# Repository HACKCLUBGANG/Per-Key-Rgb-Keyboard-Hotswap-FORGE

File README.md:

# Per-Key-Led-Keyboard-Hotswap-FORGE

Source Link Onshape -  https://cad.onshape.com/documents/a3706bff300e93766397b60f/w/be6071b581e0c225a171638b/e/79bd546bad59e5e5cdb5a4cd?renderMode=0&uiState=6af5ff969d34894ea51fd6a4
---------------------------------------
Render

Onshape

This is the Per-Key-Led-Keyboard-Hotswap which says in its name that it has per key ice blue led
It also has kailh hotswap attachment so u can also switch keys without worrying about opening the keyboard
Each key has a south facing smd ice blue led under the switch.

Heres A Render Of The Whole Build

https://github.com/user-attachments/assets/ba00d72b-443f-43d3-ab56-3a87e9c14a67

# Features 
- Per Key Rgb Customizable
- Hotswappable
- Compact  60%  10.1cm X 29.2 cm
- Usb C Powered
- 3d Printed Case
- Rp Pi Pico Fitted Into A Compact Keyboard
- 2 Layer Pcb
- Custom Made Led Circuitry
 Cool Looking :>

# Schematics 
Files in /PcbandSchem

#  Printed Circuit Board PCB
Files in /PcbandSchem

Front  Copper 

Back Copper

Both Layers

# Cad
Files in /CAD
Bottom   Plate

Top Plate

Both

# BOM
| # | Component | Part Number / Model | Qty Needed | Qty Purchased | Price (INR) | Product Link |
|---:|---|---|---:|---:|---:|---|
| 1 | Custom PCB + Shipping | JLCPCB FR-4 | 1 | 1 | ~2665 | [JLCPCB](https://jlcpcb.com/) |
| 2 | Microcontroller | Raspberry Pi Pico (RP2040) | 1 | 1 | 422 | [Robu](https://robu.in/) |
| 3 | USB-C Female Connector | Hroparts TYPE-C-31-M-13A (R250302) | 1 | 1 | 27 | [Robu](https://robu.in/product/type-c-31-m-13a-hroparts-5a-1-recessed-mount-16p-female-30%e2%84%8380-type-c-smd-usb-connectors-rohs/) |
| 4 | USB-A to Micro-USB Cable | 80cm | 1 | 1 | 59 | [Robu](https://robu.in/) |
| 5 | Micro-USB Male Connector | YT2153Y | 1 | 1 | 79 | [Robu](https://robu.in/) |
| 6 | LED Driver IC | TLC5948APWPR | 4 | 4 | 1144 | [Robu](https://robu.in/) |
| 7 | Ice-Blue LEDs | XINGLIGHT XL-2835BGWC-05 | 61 | 85 | 102 | [Robu](https://robu.in/) |
| 8 | Switching Diodes | Slkor 1N4148W SOD-123 | 61 | 70 | 72.80 | [Robu](https://robu.in/) |
| 9 | Ceramic Capacitors | 100nF, 1206, 50V | 4 | 4 | 32 | [Robu](https://robu.in/) |
| 10 | Bulk Capacitor | Taiyo Yuden EMK325ABJ107MM-T, 100µF 16V | 1 | 1 | 292.19* | [Taiyo Yuden](https://www.yuden.co.jp/) |
| 11 | Resistors | 10kΩ, 1206 | 4 | 12 | 10.56 | [Robu](https://robu.in/) |
| 12 | Resistors | 5.1kΩ, 1206 | 2 | 48 | 10.08 | [Robu](https://robu.in/) |
| 13 | Resistors | Yageo AC1206FR-07200RL, 200Ω | 0 required for IREF | 25 | 10.25 | [Robu](https://robu.in/) |
| 14 | Mechanical Switches | Gateron G Pro 3.0 Yellow | 61 | 70 (7 packs) | 1253.70 | [Meckeys](https://meckeys.com/) |
| 15 | Hot-Swap Sockets | Kailh MX Hot-Swap Socket, White | 61 | 7 listings | 504 | [Meckeys](https://meckeys.com/) |
| 16 | Stabilizers | DesignerStudio Plate Stabilizers | 4 × 2U + 1 × 6.25U | 1 kit | 550 | [Keyora](https://keyora.store/products/designerstudio-100-plate-mount-stabilizers-adaptive-wire-pom) |
| 17 | Keycaps | Selected keycap set | 1 set | 1 set | 799 | — |

## Notes
- Robu has a minimum order value of ₹10 per item.
- PCB + shipping is approximately $29 (₹2,665).

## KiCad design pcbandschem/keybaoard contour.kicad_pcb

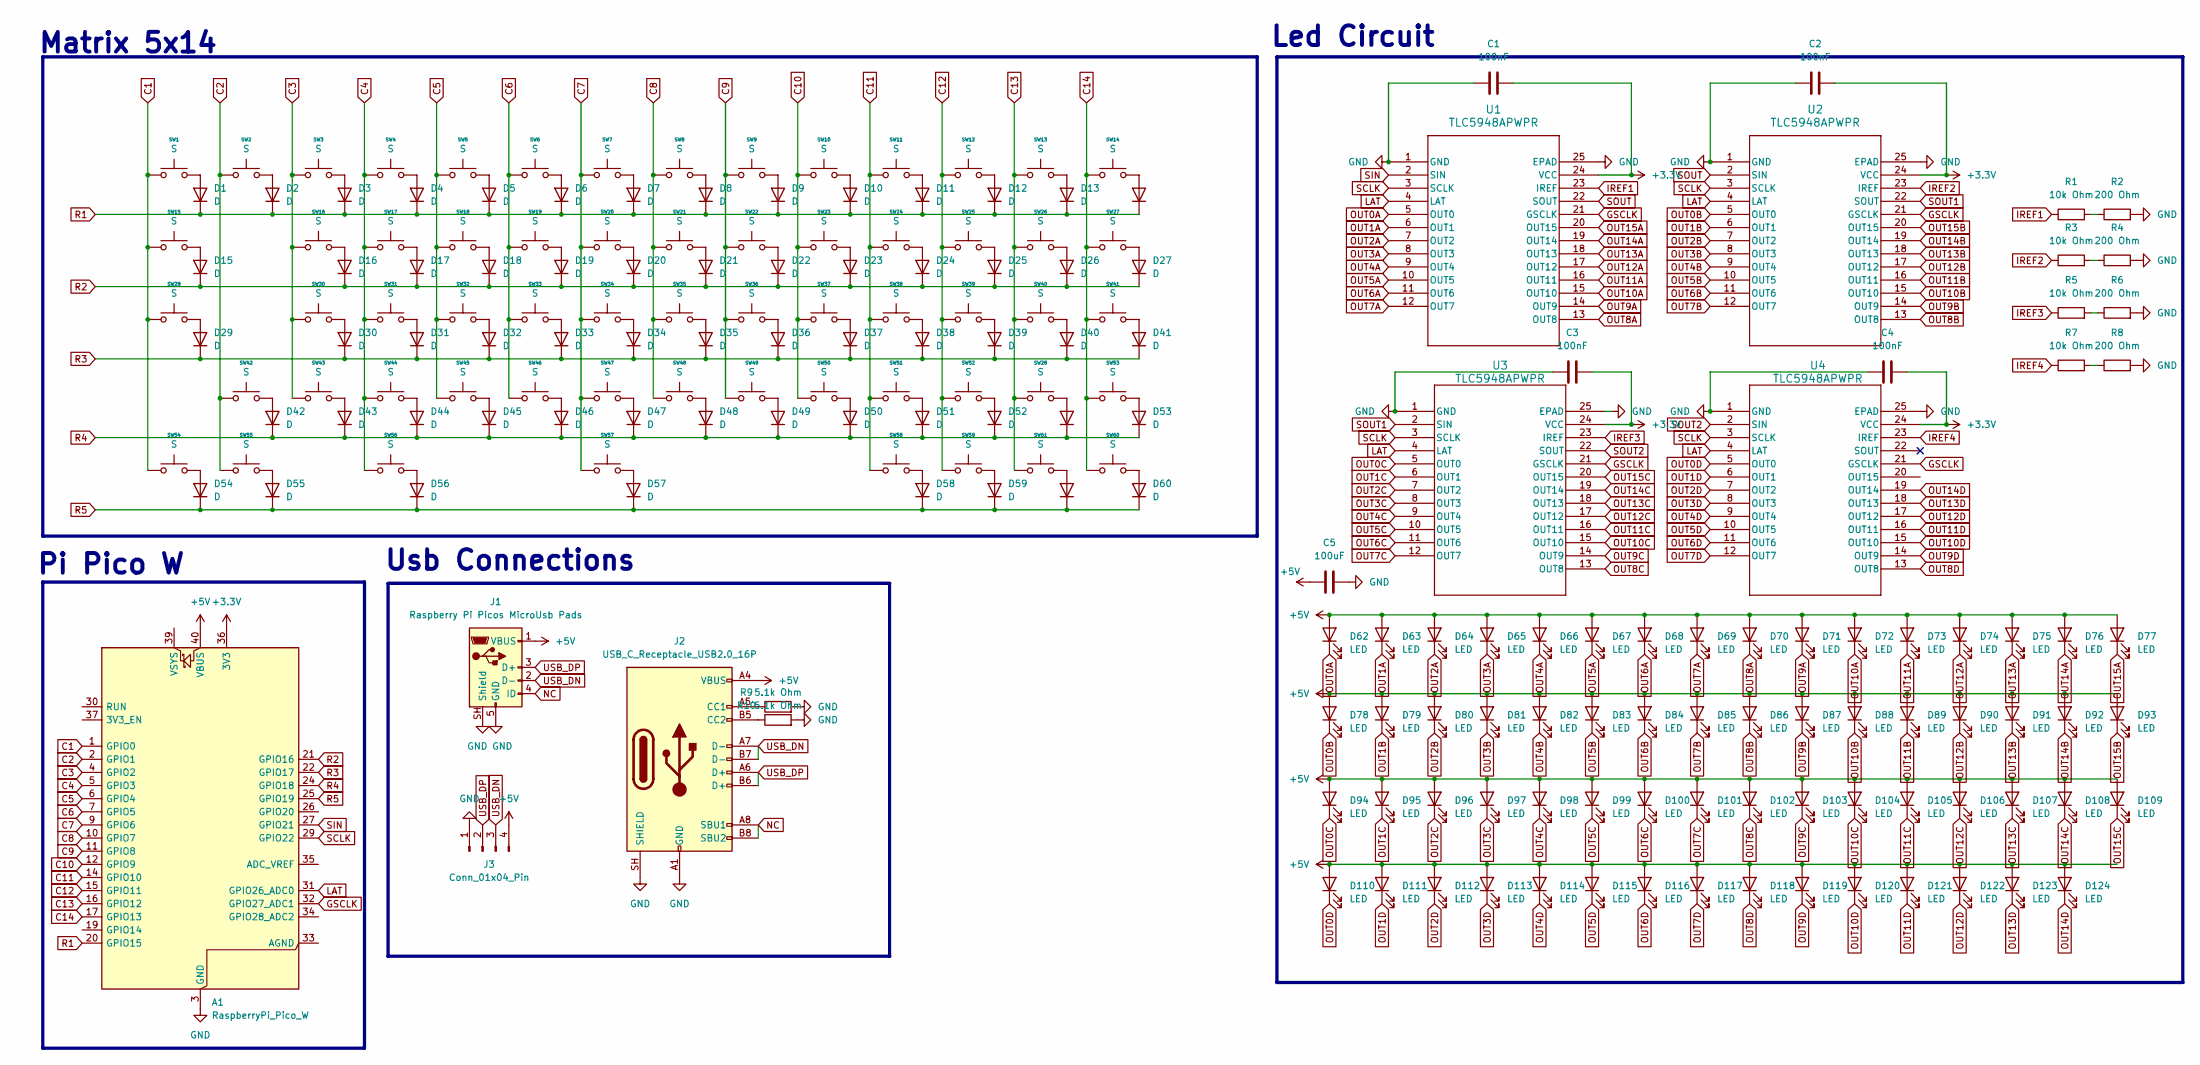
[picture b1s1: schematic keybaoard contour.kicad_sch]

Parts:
A1: RaspberryPi_Pico_W; RaspberryPi_Pico_SMD
C1, C2, C3, C4: 100nF; C_1206_3216Metric_Pad1.33x1.80mm_HandSolder
C5: 100uF; C_1210_3225Metric_Pad1.33x2.70mm_HandSolder
D1, D2, D3, D4, D5, D6, D7, D8, D9, D10, D11, D12, D13, D14, D15, D16, D17, D18, D19, D20, D21, D22, D23, D24, D25, D26, D27, D28, D29, D30, D31, D32, D33, D34, D35, D36, D37, D38, D39, D40, D41, D42, D43, D44, D45, D46, D47, D48, D49, D50, D51, D52, D53, D54, D55, D56, D57, D58, D59, D60, D61: D; D_SOD-123
D62, D63, D64, D65, D66, D67, D68, D69, D70, D71, D72, D73, D74, D75, D76, D77, D78, D79, D80, D81, D82, D83, D84, D85, D86, D87, D88, D89, D90, D91, D92, D93, D94, D95, D96, D97, D98, D99, D100, D101, D102, D103, D104, D105, D106, D107, D108, D109, D110, D111, D112, D113, D114, D115, D116, D117, D118, D119, D120, D121, D122, D123, D124: LED; LED_PLCC_2835_Handsoldering
J1: Raspberry Pi Picos MicroUsb Pads
J2: USB_C_Receptacle_USB2.0_16P; USB-C-SMD_TYPE-C-31-M-13C
J3: Conn_01x04_Pin; PinHeader_1x04_P2.54mm_Vertical
R1, R3, R5, R7: 10k Ohm; R_1206_3216Metric_Pad1.30x1.75mm_HandSolder
R2, R4, R6, R8: 200 Ohm; R_1206_3216Metric_Pad1.30x1.75mm_HandSolder
R9, R10: 5.1k Ohm; R_1206_3216Metric_Pad1.30x1.75mm_HandSolder
SW1, SW2, SW3, SW4, SW5, SW6, SW7, SW8, SW9, SW10, SW11, SW12, SW13, SW14, SW15, SW16, SW17, SW18, SW19, SW20, SW21, SW22, SW23, SW24, SW25, SW26, SW27, SW28, SW29, SW30, SW31, SW32, SW33, SW34, SW35, SW36, SW37, SW38, SW39, SW40, SW41, SW42, SW43, SW44, SW45, SW46, SW47, SW48, SW49, SW50, SW51, SW52, SW53, SW54, SW55, SW56, SW57, SW58, SW59, SW60, SW61: S; Kailh_socket_MX
U1, U2, U3, U4: TLC5948APWPR; PWP24_2P4X2P98_TEX

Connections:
+3.3V: A1.36 (3V3), C1.2, C2.2, C3.2, C4.2, U1.24 (VCC), U2.24 (VCC), U3.24 (VCC), U4.24 (VCC)
+5V: A1.40 (VBUS), C5.1, D62.2 (A), D63.2 (A), D64.2 (A), D65.2 (A), D66.2 (A), D67.2 (A), D68.2 (A), D69.2 (A), D70.2 (A), D71.2 (A), D72.2 (A), D73.2 (A), D74.2 (A), D75.2 (A), D76.2 (A), D77.2 (A), D78.2 (A), D79.2 (A), D80.2 (A), D81.2 (A), D82.2 (A), D83.2 (A), D84.2 (A), D85.2 (A), D86.2 (A), D87.2 (A), D88.2 (A), D89.2 (A), D90.2 (A), D91.2 (A), D92.2 (A), D93.2 (A), D94.2 (A), D95.2 (A), D96.2 (A), D97.2 (A), D98.2 (A), D99.2 (A), D100.2 (A), D101.2 (A), D102.2 (A), D103.2 (A), D104.2 (A), D105.2 (A), D106.2 (A), D107.2 (A), D108.2 (A), D109.2 (A), D110.2 (A), D111.2 (A), D112.2 (A), D113.2 (A), D114.2 (A), D115.2 (A), D116.2 (A), D117.2 (A), D118.2 (A), D119.2 (A), D120.2 (A), D121.2 (A), D122.2 (A), D123.2 (A), D124.2 (A), J1.1 (VBUS), J2.A4 (VBUS), J2.A9 (VBUS), J2.B4 (VBUS), J2.B9 (VBUS), J3.4
C1: A1.1 (GPIO0), SW1.1, SW15.1, SW29.1, SW54.1
C2: A1.2 (GPIO1), SW2.1, SW42.1, SW55.1
C3: A1.4 (GPIO2), SW3.1, SW16.1, SW30.1, SW43.1
C4: A1.5 (GPIO3), SW4.1, SW17.1, SW31.1, SW44.1, SW56.1
C5: A1.6 (GPIO4), SW5.1, SW18.1, SW32.1, SW45.1
C6: A1.7 (GPIO5), SW6.1, SW19.1, SW33.1, SW46.1
C7: A1.9 (GPIO6), SW7.1, SW20.1, SW34.1, SW47.1, SW57.1
C8: A1.10 (GPIO7), SW8.1, SW21.1, SW35.1, SW48.1
C9: A1.11 (GPIO8), SW9.1, SW22.1, SW36.1, SW49.1
C10: A1.12 (GPIO9), SW10.1, SW23.1, SW37.1, SW50.1
C11: A1.14 (GPIO10), SW11.1, SW24.1, SW38.1, SW51.1, SW58.1
C12: A1.15 (GPIO11), SW12.1, SW25.1, SW39.1, SW52.1, SW59.1
C13: A1.16 (GPIO12), SW13.1, SW26.1, SW28.1, SW40.1, SW61.1
C14: A1.17 (GPIO13), SW14.1, SW27.1, SW41.1, SW53.1, SW60.1
GND: A1.3 (GND), A1.8 (GND), A1.13 (GND), A1.18 (GND), A1.23 (GND), A1.28 (GND), A1.38 (GND), C1.1, C2.1, C3.1, C4.1, C5.2, J1.5 (GND), J1.SH (Shield), J2.A1 (GND), J2.A12 (GND), J2.B1 (GND), J2.B12 (GND), J2.SH (SHIELD), J3.1, R2.2, R4.2, R6.2, R8.2, R9.2, R10.2, U1.1 (GND), U1.25 (EPAD), U2.1 (GND), U2.25 (EPAD), U3.1 (GND), U3.25 (EPAD), U4.1 (GND), U4.25 (EPAD)
GSCLK: A1.32 (GPIO27_ADC1), U1.21 (GSCLK), U2.21 (GSCLK), U3.21 (GSCLK), U4.21 (GSCLK)
IREF1: R1.1, U1.23 (IREF)
IREF2: R3.1, U2.23 (IREF)
IREF3: R5.1, U3.23 (IREF)
IREF4: R7.1, U4.23 (IREF)
LAT: A1.31 (GPIO26_ADC0), U1.4 (LAT), U2.4 (LAT), U3.4 (LAT), U4.4 (LAT)
NC: J1.4 (ID), J2.A8 (SBU1), J2.B8 (SBU2)
unnamed: D1.2 (A), SW1.2
unnamed: D2.2 (A), SW2.2
unnamed: D3.2 (A), SW3.2
unnamed: D4.2 (A), SW4.2
unnamed: D5.2 (A), SW5.2
unnamed: D6.2 (A), SW6.2
unnamed: D7.2 (A), SW7.2
unnamed: D8.2 (A), SW8.2
unnamed: D9.2 (A), SW9.2
unnamed: D10.2 (A), SW10.2
unnamed: D11.2 (A), SW11.2
unnamed: D12.2 (A), SW12.2
unnamed: D13.2 (A), SW13.2
unnamed: D14.2 (A), SW14.2
unnamed: D15.2 (A), SW15.2
unnamed: D16.2 (A), SW16.2
unnamed: D17.2 (A), SW17.2
unnamed: D18.2 (A), SW18.2
unnamed: D19.2 (A), SW19.2
unnamed: D20.2 (A), SW20.2
unnamed: D21.2 (A), SW21.2
unnamed: D22.2 (A), SW22.2
unnamed: D23.2 (A), SW23.2
unnamed: D24.2 (A), SW24.2
unnamed: D25.2 (A), SW25.2
unnamed: D26.2 (A), SW26.2
unnamed: D27.2 (A), SW27.2
unnamed: D28.2 (A), SW28.2
unnamed: D29.2 (A), SW29.2
unnamed: D30.2 (A), SW30.2
unnamed: D31.2 (A), SW31.2
unnamed: D32.2 (A), SW32.2
unnamed: D33.2 (A), SW33.2
unnamed: D34.2 (A), SW34.2
unnamed: D35.2 (A), SW35.2
unnamed: D36.2 (A), SW36.2
unnamed: D37.2 (A), SW37.2
unnamed: D38.2 (A), SW38.2
unnamed: D39.2 (A), SW39.2
unnamed: D40.2 (A), SW40.2
unnamed: D41.2 (A), SW41.2
unnamed: D42.2 (A), SW42.2
unnamed: D43.2 (A), SW43.2
unnamed: D44.2 (A), SW44.2
unnamed: D45.2 (A), SW45.2
unnamed: D46.2 (A), SW46.2
unnamed: D47.2 (A), SW47.2
unnamed: D48.2 (A), SW48.2
unnamed: D49.2 (A), SW49.2
unnamed: D50.2 (A), SW50.2
unnamed: D51.2 (A), SW51.2
unnamed: D52.2 (A), SW52.2
unnamed: D53.2 (A), SW53.2
unnamed: D54.2 (A), SW54.2
unnamed: D55.2 (A), SW55.2
unnamed: D56.2 (A), SW56.2
unnamed: D57.2 (A), SW57.2
unnamed: D58.2 (A), SW58.2
unnamed: D59.2 (A), SW59.2
unnamed: D60.2 (A), SW60.2
unnamed: D61.2 (A), SW61.2
unnamed: J2.A5 (CC1), R9.1
unnamed: J2.B5 (CC2), R10.1
unnamed: R1.2, R2.1
unnamed: R3.2, R4.1
unnamed: R5.2, R6.1
unnamed: R7.2, R8.1
OUT0A: D62.1 (K), U1.5 (OUT0)
OUT0B: D78.1 (K), U2.5 (OUT0)
OUT0C: D94.1 (K), U3.5 (OUT0)
OUT0D: D110.1 (K), U4.5 (OUT0)
OUT1A: D63.1 (K), U1.6 (OUT1)
OUT1B: D79.1 (K), U2.6 (OUT1)
OUT1C: D95.1 (K), U3.6 (OUT1)
OUT1D: D111.1 (K), U4.6 (OUT1)
OUT2A: D64.1 (K), U1.7 (OUT2)
OUT2B: D80.1 (K), U2.7 (OUT2)
OUT2C: D96.1 (K), U3.7 (OUT2)
OUT2D: D112.1 (K), U4.7 (OUT2)
OUT3A: D65.1 (K), U1.8 (OUT3)
OUT3B: D81.1 (K), U2.8 (OUT3)
OUT3C: D97.1 (K), U3.8 (OUT3)
OUT3D: D113.1 (K), U4.8 (OUT3)
OUT4A: D66.1 (K), U1.9 (OUT4)
OUT4B: D82.1 (K), U2.9 (OUT4)
OUT4C: D98.1 (K), U3.9 (OUT4)
OUT4D: D114.1 (K), U4.9 (OUT4)
OUT5A: D67.1 (K), U1.10 (OUT5)
OUT5B: D83.1 (K), U2.10 (OUT5)
OUT5C: D99.1 (K), U3.10 (OUT5)
OUT5D: D115.1 (K), U4.10 (OUT5)
OUT6A: D68.1 (K), U1.11 (OUT6)
OUT6B: D84.1 (K), U2.11 (OUT6)
OUT6C: D100.1 (K), U3.11 (OUT6)
OUT6D: D116.1 (K), U4.11 (OUT6)
OUT7A: D69.1 (K), U1.12 (OUT7)
OUT7B: D85.1 (K), U2.12 (OUT7)
OUT7C: D101.1 (K), U3.12 (OUT7)
OUT7D: D117.1 (K), U4.12 (OUT7)
OUT8A: D70.1 (K), U1.13 (OUT8)
OUT8B: D86.1 (K), U2.13 (OUT8)
OUT8C: D102.1 (K), U3.13 (OUT8)
OUT8D: D118.1 (K), U4.13 (OUT8)
OUT9A: D71.1 (K), U1.14 (OUT9)
OUT9B: D87.1 (K), U2.14 (OUT9)
OUT9C: D103.1 (K), U3.14 (OUT9)
OUT9D: D119.1 (K), U4.14 (OUT9)
OUT10A: D72.1 (K), U1.15 (OUT10)
OUT10B: D88.1 (K), U2.15 (OUT10)
OUT10C: D104.1 (K), U3.15 (OUT10)
OUT10D: D120.1 (K), U4.15 (OUT10)
OUT11A: D73.1 (K), U1.16 (OUT11)
OUT11B: D89.1 (K), U2.16 (OUT11)
OUT11C: D105.1 (K), U3.16 (OUT11)
OUT11D: D121.1 (K), U4.16 (OUT11)
OUT12A: D74.1 (K), U1.17 (OUT12)
OUT12B: D90.1 (K), U2.17 (OUT12)
OUT12C: D106.1 (K), U3.17 (OUT12)
OUT12D: D122.1 (K), U4.17 (OUT12)
OUT13A: D75.1 (K), U1.18 (OUT13)
OUT13B: D91.1 (K), U2.18 (OUT13)
OUT13C: D107.1 (K), U3.18 (OUT13)
OUT13D: D123.1 (K), U4.18 (OUT13)
OUT14A: D76.1 (K), U1.19 (OUT14)
OUT14B: D92.1 (K), U2.19 (OUT14)
OUT14C: D108.1 (K), U3.19 (OUT14)
OUT14D: D124.1 (K), U4.19 (OUT14)
OUT15A: D77.1 (K), U1.20 (OUT15)
OUT15B: D93.1 (K), U2.20 (OUT15)
OUT15C: D109.1 (K), U3.20 (OUT15)
R1: A1.20 (GPIO15), D1.1 (K), D2.1 (K), D3.1 (K), D4.1 (K), D5.1 (K), D6.1 (K), D7.1 (K), D8.1 (K), D9.1 (K), D10.1 (K), D11.1 (K), D12.1 (K), D13.1 (K), D14.1 (K)
R2: A1.21 (GPIO16), D15.1 (K), D16.1 (K), D17.1 (K), D18.1 (K), D19.1 (K), D20.1 (K), D21.1 (K), D22.1 (K), D23.1 (K), D24.1 (K), D25.1 (K), D26.1 (K), D27.1 (K)
R3: A1.22 (GPIO17), D29.1 (K), D30.1 (K), D31.1 (K), D32.1 (K), D33.1 (K), D34.1 (K), D35.1 (K), D36.1 (K), D37.1 (K), D38.1 (K), D39.1 (K), D40.1 (K), D41.1 (K)
R4: A1.24 (GPIO18), D28.1 (K), D42.1 (K), D43.1 (K), D44.1 (K), D45.1 (K), D46.1 (K), D47.1 (K), D48.1 (K), D49.1 (K), D50.1 (K), D51.1 (K), D52.1 (K), D53.1 (K)
R5: A1.25 (GPIO19), D54.1 (K), D55.1 (K), D56.1 (K), D57.1 (K), D58.1 (K), D59.1 (K), D60.1 (K), D61.1 (K)
SCLK: A1.29 (GPIO22), U1.3 (SCLK), U2.3 (SCLK), U3.3 (SCLK), U4.3 (SCLK)
SIN: A1.27 (GPIO21), U1.2 (SIN)
SOUT: U1.22 (SOUT), U2.2 (SIN)
SOUT1: U2.22 (SOUT), U3.2 (SIN)
SOUT2: U3.22 (SOUT), U4.2 (SIN)
USB_DN: J1.2 (D-), J2.A7 (D-), J2.B7 (D-), J3.3
USB_DP: J1.3 (D+), J2.A6 (D+), J2.B6 (D+), J3.2

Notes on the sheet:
Led Circuit
Matrix 5x14
Pi Pico W
Usb Connections

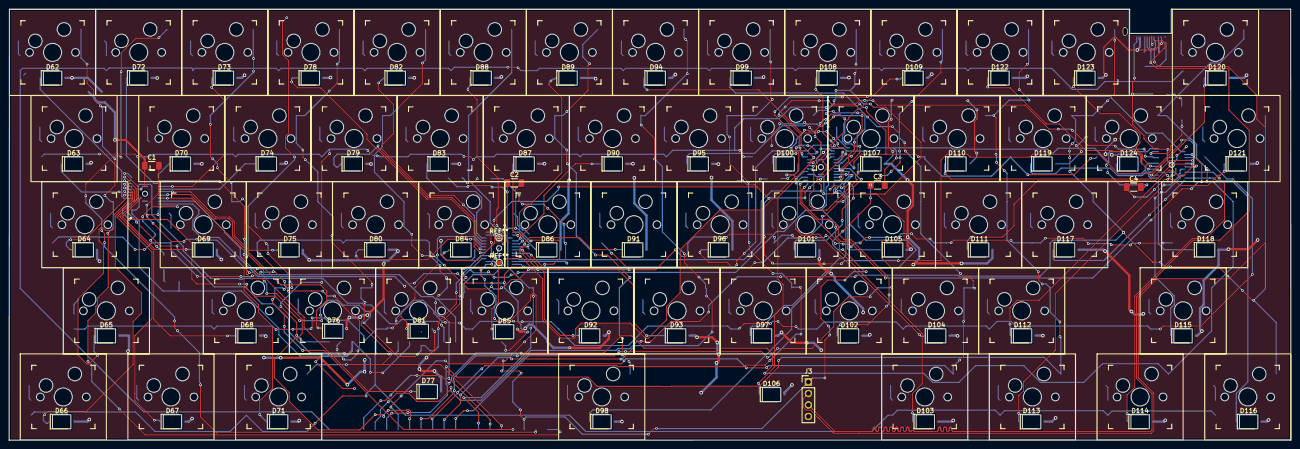
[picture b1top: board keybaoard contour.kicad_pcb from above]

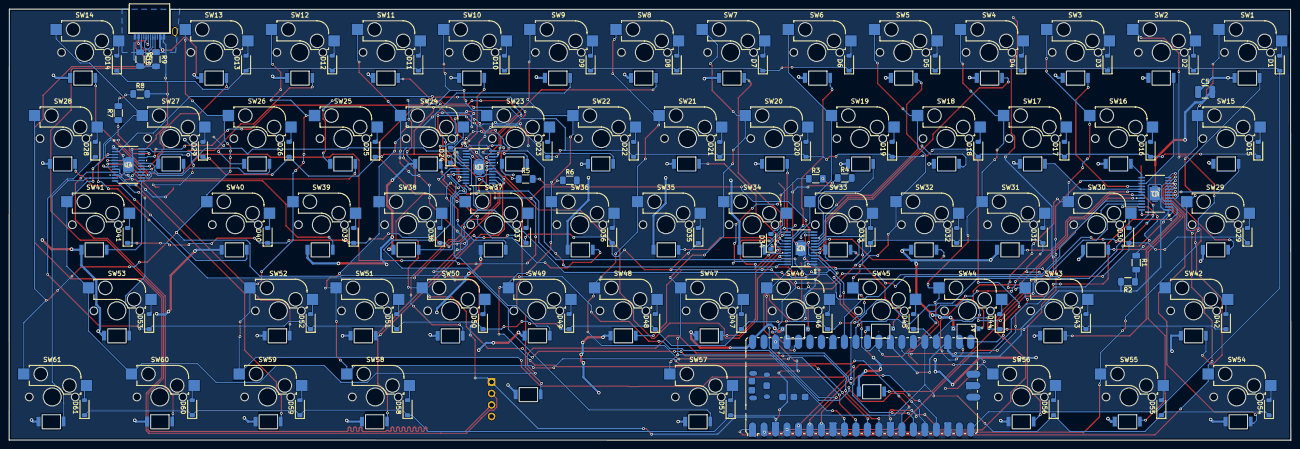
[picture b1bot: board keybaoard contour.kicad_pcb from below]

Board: 2 copper layers, 283.4 x 95.3 mm, 207 parts (78 on the bottom side), 166 nets.
